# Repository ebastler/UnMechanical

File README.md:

# UnMechanical
 Unmechanical is an attempt to create a capacitive touch keyboard, replacing switches with touchpads.

 The operating principle is pretty much unchanged from the EC boards by [cipulot](https://github.com/Cipulot). Basically, the columns are strobed by the MCU, and the capacitive touchpad forms a capacitive voltage divider together with a 220pF resistor on the PCB. The voltage over the capacitor is measured to determine the capacity of the touchpad, which strongly changes if the pad is touched.

 In order to be able to scan multiple rows, the board uses an analog mux chip that switches from row to row. The input signal is amplified by an OPAMP, since QMK does not offer support for the STM32G431 built-in OPAMPs yet.

## Sweepish
So far, this repository contains a single board, "Sweepish", which consists of a Sweep 3x5 alpha cluster, and a modified 3 key thumb cluster. 

### Features:
* 36 capacitive touch-keys (Layout similar to Sweep)
* Magnetic split connect, allowing for unibody-use
* USB-C PD peripheral of the STM32G431 chip connected to USB-C port
* Circuitry and hole in PCB to mount a Switch Joycon haptic actuator and use it for typing feedback

The board is designed to be used as a unibody, held together by HytePro M411P magnetic pogo connectors, but can also be made into a "proper" split board by using a magnetic cable assembly instead.

Firmware support, as well as some optimizations to make the board nicer to use, are still being worked on (so far it can only work as a single half, split EC keyscan does not work yet). The repo is only published as a proof-of-concept - more or less what the entire board design was for, in the first place. 

This keyboard also uses the USB-C PD peripheral of the STM32G431 since I wanted to make a test-board to experiment using it.

### Pictures

A short video showing the board in action can be found on my youtube channel: https://youtu.be/7uHqJic0PQ8

## Thanks
* [cipulot](https://github.com/Cipulot) for his EC boards, EC QMK keyscan firmwares and help in developing this PCB
* [PCBWay](https://www.pcbway.com/) for the gorgeous sponsored PCBs - couldn't have done it without you!

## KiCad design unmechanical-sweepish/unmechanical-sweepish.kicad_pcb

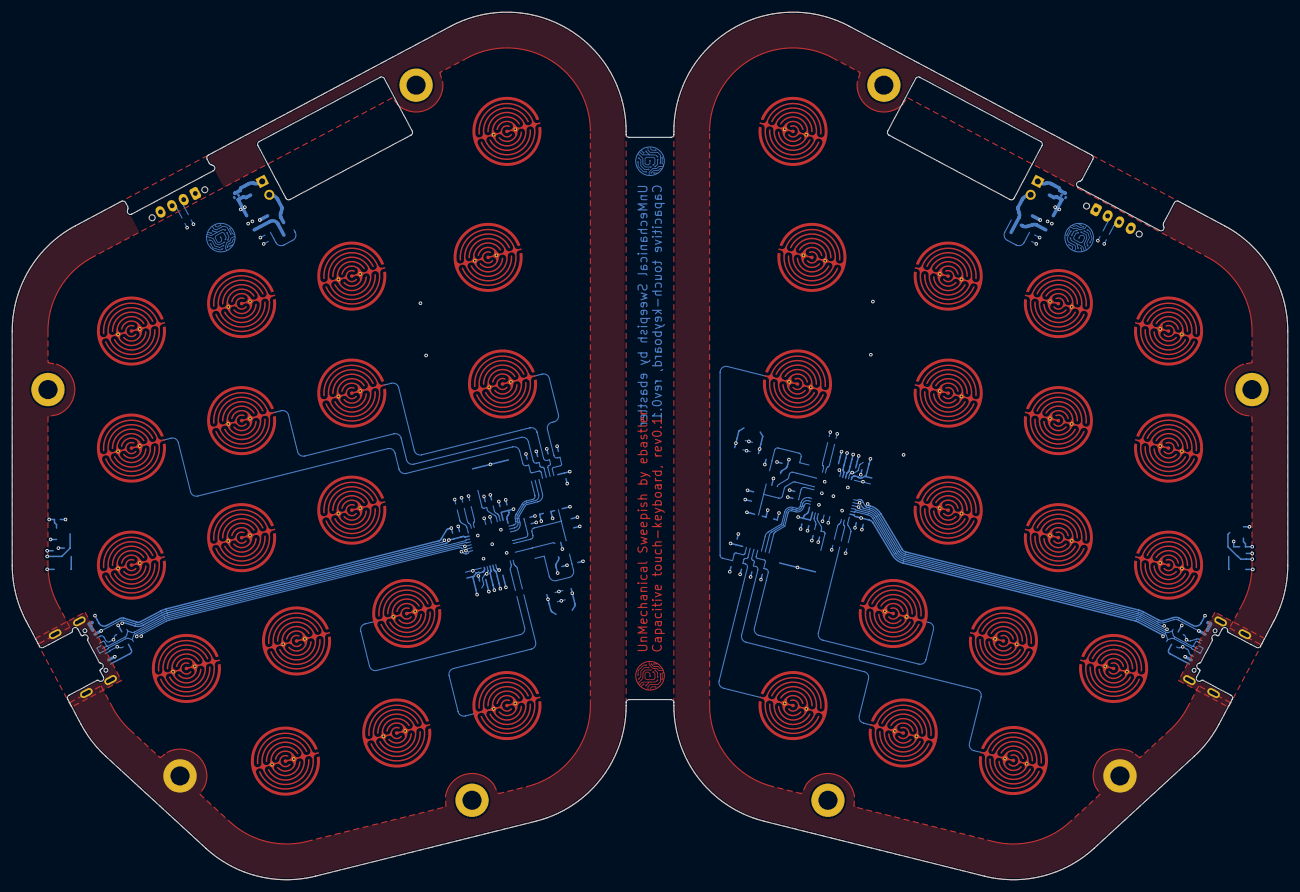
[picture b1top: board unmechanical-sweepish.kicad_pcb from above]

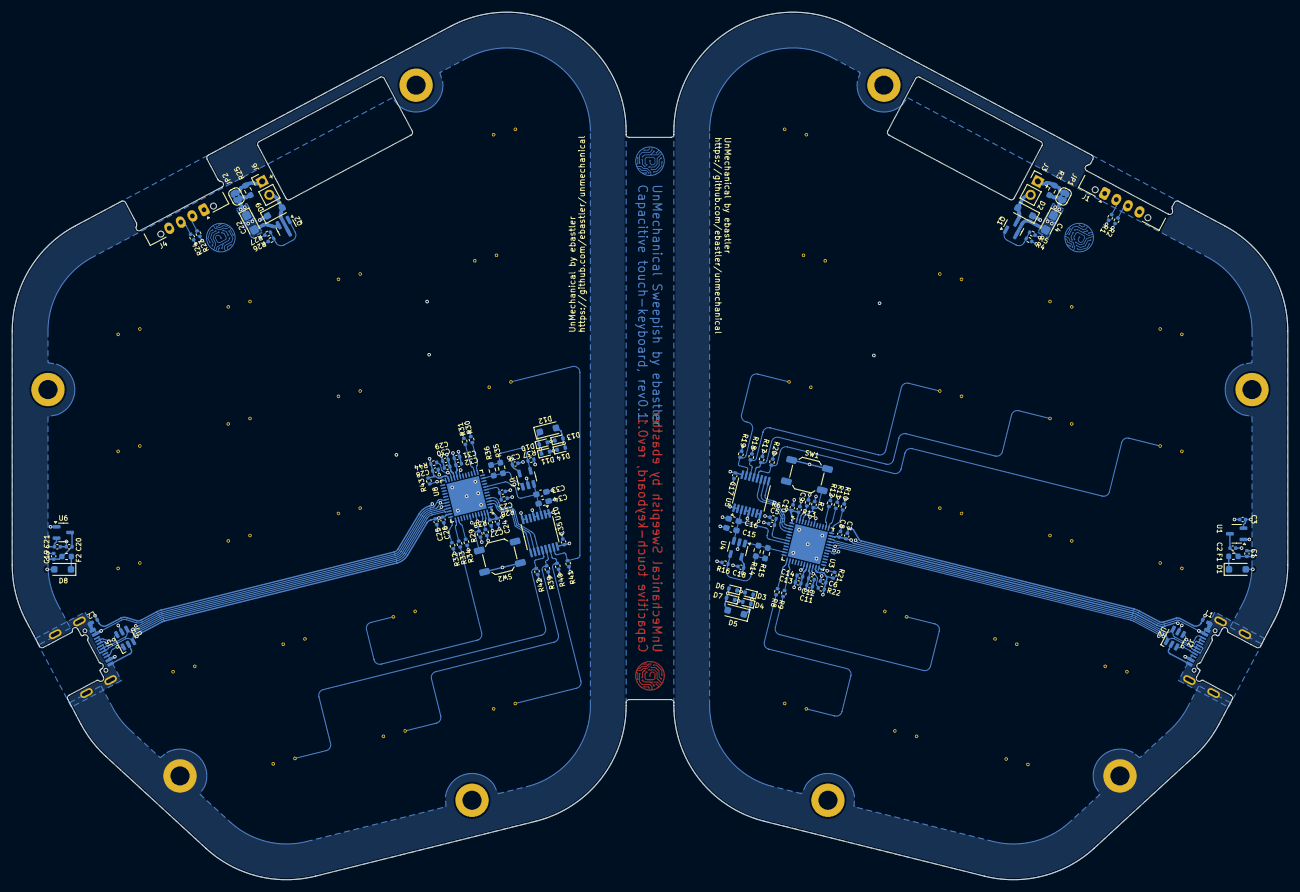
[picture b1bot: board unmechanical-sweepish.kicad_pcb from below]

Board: 4 copper layers, 214.0 x 145.5 mm, 164 parts (120 on the bottom side), 82 nets.

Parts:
C1, C7, C19, C25: 4u7; C_0402_1005Metric
C2, C3, C11, C13, C20, C21, C29, C31: 1u; C_0402_1005Metric
C4, C22: 10u; CP_EIA-3216-10_Kemet-I
C5, C6, C8, C9, C10, C14, C17, C18, C23, C24, C26, C27, C28, C32, C35, C36: 100n; C_0402_1005Metric
C12, C30: 10n; C_0402_1005Metric
C15, C33: DNP; C_0603_1608Metric_Pad1.08x0.95mm_HandSolder
C16, C34: 220p; C_0603_1608Metric_Pad1.08x0.95mm_HandSolder
D1, D2, D8, D9: D_Schottky; D_SOD-123F
D3, D4, D6, D7, D10, D11, D13, D14: 1N4148WT; D_SOD-523
D5, D12: SMF3.3; D_SOD-123F
EC1, EC2, EC3, EC4, EC5, EC6, EC7, EC8, EC9, EC10, EC11, EC12, EC13, EC14, EC15, EC16, EC17, EC18, EC19, EC20, EC21, EC22, EC23, EC24, EC25, EC26, EC27, EC28, EC29, EC30, EC31, EC32, EC33, EC34, EC35, EC36: EC; capsense_finger_1
F1, F2: Polyfuse; Fuse_0603_1608Metric
H1, H2, H3, H4, H5, H6, H7, H8: screw; MountingHole_3.2mm_M3_DIN965_Pad
J1: HytePro M; CON_HytePro_M411P_Plug_1x04-P2.20mm_Horizontal_FlushMount
J2, J5: USB_C_Receptacle_USB2.0; USB_C_Receptacle_HRO_TYPE-C-31-M-14
J3, J6: M; PinHeader_1x02_P2.54mm_Vertical
J4: HytePro F; CON_HytePro_M411P_Receptacle_1x04-P2.20mm_Horizontal_FlushM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
JP1, JP2: JP; SolderJumper-2_P1.3mm_Bridged2Bar_RoundedPad1.0x1.5mm
L1, L2: BLM15PX121SN1D; L_0402_1005Metric
Q1, Q2: AO3400A; SOT-23
R1, R2, R4, R8, R9, R10, R11, R12, R23, R24, R26, R30, R31, R32, R33, R34: 100R; R_0402_1005Metric
R3, R25: 4R7; R_0603_1608Metric_Pad0.98x0.95mm_HandSolder
R5, R6, R7, R13, R27, R28, R29, R38: 10k; R_0402_1005Metric
R14, R35: 100k; R_0603_1608Metric_Pad0.98x0.95mm_HandSolder
R15, R36: DNP; R_0603_1608Metric_Pad0.98x0.95mm_HandSolder
R16, R37: 1k; R_0402_1005Metric
R17, R18, R19, R20, R39, R40, R41, R42: 100k; R_0402_1005Metric
R21, R22, R43, R44: 4k7; R_0402_1005Metric
SW1, SW2: B/R; SW_SPST_SKQG_WithStem
U1, U6: XC6206PxxxMR; SOT-23-3
U2, U7: SRV05-4; SOT-23-6-routable
U3, U8: STM32G431CBUx; QFN-48-1EP_7x7mm_P0.5mm_EP5.6x5.6mm
U4, U9: OPA340NA; SOT-23-5
U5, U10: 74HC4051; TSSOP-16_4.4x5mm_P0.65mm

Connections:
+3.3V: C21.1, C24.1, C25.1, C26.1, C27.1, C28.1, C29.1, C30.1, C31.1, C32.1, C35.1, C36.1, D10.1 (K), D11.1 (K), D12.1 (K), R28.1, R43.1, R44.1, SW2.1, U6.2 (VO), U8.1 (VBAT), U8.20 (VREF+), U8.21 (VDDA), U8.23 (VDD), U8.35 (VDD), U8.48 (VDD), U9.5 (V+), U10.16 (VCC)
+3V3: C3.1, C6.1, C7.1, C8.1, C9.1, C10.1, C11.1, C12.1, C13.1, C14.1, C17.1, C18.1, D3.1 (K), D4.1 (K), D5.1 (K), R6.1, R13.2, R21.1, R22.1, SW1.1, U1.2 (VO), U3.1 (VBAT), U3.20 (VREF+), U3.21 (VDDA), U3.23 (VDD), U3.35 (VDD), U3.48 (VDD), U4.5 (V+), U5.16 (VCC)
+5V: C1.1, C2.1, C4.1, D2.1 (K), F1.2, J1.1, JP1.2 (B), R3.1, U1.3 (VI), U2.5 (VP)
+5VL: C19.1, C20.1, C22.1, D9.1 (K), F2.2, J4.1, JP2.2 (B), R25.1, U6.3 (VI), U7.5 (VP)
/unmechanical-sweepish-l/ADC: R14.2, R15.2, U3.11 (PA3), U4.1
/unmechanical-sweepish-l/BOOT0: R7.1, SW1.2, U3.46 (PB8)
/unmechanical-sweepish-l/CC1: J2.A5 (CC1), U2.3 (IO2), U3.31 (PA9), U3.44 (PB6)
/unmechanical-sweepish-l/CC2: J2.B5 (CC2), U2.4 (IO3), U3.32 (PA10), U3.42 (PB4)
/unmechanical-sweepish-l/USART3_RX: D3.2 (A), D6.1 (K), R2.1, R21.2, U3.24 (PB11)
/unmechanical-sweepish-l/USART3_TX: D4.2 (A), D7.1 (K), R1.1, R22.2, U3.22 (PB10)
/unmechanical-sweepish-l/USBGND: H1.1, J2.A1 (GND), J2.A12 (GND), J2.B1 (GND), J2.B12 (GND), J2.S1 (SHIELD), L1.1, U2.2 (VN)
/unmechanical-sweepish-l/USB_D+: J2.A6 (D+), J2.B6 (D+), U2.6 (IO4), U3.34 (PA12)
/unmechanical-sweepish-l/USB_D-: J2.A7 (D-), J2.B7 (D-), U2.1 (IO1), U3.33 (PA11)
/unmechanical-sweepish-l/VBUS: D1.2 (A), J2.A4 (VBUS), J2.A9 (VBUS), J2.B4 (VBUS), J2.B9 (VBUS), U3.30 (PA8)
/unmechanical-sweepish-l/amux_sel_0: U3.4 (PC15), U5.11 (S0)
/unmechanical-sweepish-l/amux_sel_1: U3.3 (PC14), U5.10 (S1)
/unmechanical-sweepish-l/amux_sel_2: U3.2 (PC13), U5.9 (S2)
/unmechanical-sweepish-l/aplex_out: C15.1, C16.1, U3.8 (PA0), U4.3 (+), U5.3 (A)
/unmechanical-sweepish-l/c0: EC1.2 (B), EC6.2 (B), EC11.2 (B), R8.2
/unmechanical-sweepish-l/c1: EC2.2 (B), EC7.2 (B), EC12.2 (B), R9.2
/unmechanical-sweepish-l/c2: EC3.2 (B), EC8.2 (B), EC13.2 (B), EC16.2 (B), R12.2
/unmechanical-sweepish-l/c3: EC4.2 (B), EC9.2 (B), EC14.2 (B), EC17.2 (B), R11.2
/unmechanical-sweepish-l/c4: EC5.2 (B), EC10.2 (B), EC15.2 (B), EC18.2 (B), R10.2
/unmechanical-sweepish-l/handsense: R13.1, U3.47 (PB9)
/unmechanical-sweepish-l/hapt: R4.1, U3.19 (PB2)
/unmechanical-sweepish-l/nRST: C5.2, R6.2, U3.7 (PG10)
/unmechanical-sweepish-l/r0: EC1.1 (A), EC2.1 (A), EC3.1 (A), EC4.1 (A), EC5.1 (A), R20.1, U5.12 (A3)
/unmechanical-sweepish-l/r1: EC6.1 (A), EC7.1 (A), EC8.1 (A), EC9.1 (A), EC10.1 (A), R17.1, U5.13 (A0)
/unmechanical-sweepish-l/r2: EC11.1 (A), EC12.1 (A), EC13.1 (A), EC14.1 (A), EC15.1 (A), R18.1, U5.14 (A1)
/unmechanical-sweepish-l/r3: EC16.1 (A), EC17.1 (A), EC18.1 (A), R19.1, U5.15 (A2)
/unmechanical-sweepish-r/ADC: R35.2, R36.2, U8.11 (PA3), U9.1
/unmechanical-sweepish-r/BOOT0: R29.1, SW2.2, U8.46 (PB8)
/unmechanical-sweepish-r/CC1: J5.A5 (CC1), U7.6 (IO4), U8.31 (PA9), U8.44 (PB6)
/unmechanical-sweepish-r/CC2: J5.B5 (CC2), U7.1 (IO1), U8.32 (PA10), U8.42 (PB4)
/unmechanical-sweepish-r/USART3_RX: D10.2 (A), D13.1 (K), R24.1, R43.2, U8.24 (PB11)
/unmechanical-sweepish-r/USART3_TX: D11.2 (A), D14.1 (K), R23.1, R44.2, U8.22 (PB10)
/unmechanical-sweepish-r/USBGND: H5.1, J5.A1 (GND), J5.A12 (GND), J5.B1 (GND), J5.B12 (GND), J5.S1 (SHIELD), L2.1, U7.2 (VN)
/unmechanical-sweepish-r/USB_D+: J5.A6 (D+), J5.B6 (D+), U7.3 (IO2), U8.34 (PA12)
/unmechanical-sweepish-r/USB_D-: J5.A7 (D-), J5.B7 (D-), U7.4 (IO3), U8.33 (PA11)
/unmechanical-sweepish-r/VBUS: D8.2 (A), J5.A4 (VBUS), J5.A9 (VBUS), J5.B4 (VBUS), J5.B9 (VBUS), U8.30 (PA8)
/unmechanical-sweepish-r/amux_sel_0: U8.4 (PC15), U10.11 (S0)
/unmechanical-sweepish-r/amux_sel_1: U8.3 (PC14), U10.10 (S1)
/unmechanical-sweepish-r/amux_sel_2: U8.2 (PC13), U10.9 (S2)
/unmechanical-sweepish-r/aplex_out: C33.1, C34.1, U8.8 (PA0), U9.3 (+), U10.3 (A)
/unmechanical-sweepish-r/c0: EC19.2 (B), EC24.2 (B), EC29.2 (B), EC34.2 (B), R30.2
/unmechanical-sweepish-r/c1: EC20.2 (B), EC25.2 (B), EC30.2 (B), EC35.2 (B), R31.2
/unmechanical-sweepish-r/c2: EC21.2 (B), EC26.2 (B), EC31.2 (B), EC36.2 (B), R34.2
/unmechanical-sweepish-r/c3: EC22.2 (B), EC27.2 (B), EC32.2 (B), R33.2
/unmechanical-sweepish-r/c4: EC23.2 (B), EC28.2 (B), EC33.2 (B), R32.2
/unmechanical-sweepish-r/handsense: R38.1, U8.47 (PB9)
/unmechanical-sweepish-r/hapt: R26.1, U8.19 (PB2)
/unmechanical-sweepish-r/nRST: C23.2, R28.2, U8.7 (PG10)
/unmechanical-sweepish-r/r0: EC19.1 (A), EC20.1 (A), EC21.1 (A), EC22.1 (A), EC23.1 (A), R42.1, U10.12 (A3)
/unmechanical-sweepish-r/r1: EC24.1 (A), EC25.1 (A), EC26.1 (A), EC27.1 (A), EC28.1 (A), R39.1, U10.13 (A0)
/unmechanical-sweepish-r/r2: EC29.1 (A), EC30.1 (A), EC31.1 (A), EC32.1 (A), EC33.1 (A), R40.1, U10.14 (A1)
/unmechanical-sweepish-r/r3: EC34.1 (A), EC35.1 (A), EC36.1 (A), R41.1, U10.15 (A2)
GND: C1.2, C2.2, C3.2, C4.2, C5.1, C6.2, C7.2, C8.2, C9.2, C10.2, C11.2, C12.2, C13.2, C14.2, C15.2, C16.2, C17.2, C18.2, D5.2 (A), D6.2 (A), D7.2 (A), J1.4, L1.2, Q1.2 (S), R5.2, R7.2, R16.2, R17.2, R18.2, R19.2, R20.2, U1.1 (GND), U3.49 (VSS), U4.2 (V-), U5.1 (A4), U5.2 (A6), U5.4 (A7), U5.5 (A5), U5.7 (VEE), U5.8 (GND)
GND1: C19.2, C20.2, C21.2, C22.2, C23.1, C24.2, C25.2, C26.2, C27.2, C28.2, C29.2, C30.2, C31.2, C32.2, C33.2, C34.2, C35.2, C36.2, D12.2 (A), D13.2 (A), D14.2 (A), J4.4, L2.2, Q2.2 (S), R27.2, R29.2, R37.2, R38.2, R39.2, R40.2, R41.2, R42.2, U6.1 (GND), U8.49 (VSS), U9.2 (V-), U10.1 (A4), U10.2 (A6), U10.4 (A7), U10.5 (A5), U10.7 (VEE), U10.8 (GND)
unnamed: D1.1 (K), F1.1
unnamed: D2.2 (A), J3.2, Q1.3 (D)
unnamed: D8.1 (K), F2.1
unnamed: D9.2 (A), J6.2, Q2.3 (D)
unnamed: J1.2, R1.2
unnamed: J1.3, R2.2
unnamed: J3.1, JP1.1 (A), R3.2
unnamed: J4.2, R23.2
unnamed: J4.3, R24.2
unnamed: J6.1, JP2.1 (A), R25.2
unnamed: Q1.1 (G), R4.2, R5.1
unnamed: Q2.1 (G), R26.2, R27.1
unnamed: R8.1, U3.13 (PA5)
unnamed: R9.1, U3.14 (PA6)
unnamed: R10.1, U3.36 (PA13)
unnamed: R11.1, U3.37 (PA14)
unnamed: R12.1, U3.38 (PA15)
unnamed: R14.1, R15.1, R16.1, U4.4 (-)
unnamed: R30.1, U8.13 (PA5)
unnamed: R31.1, U8.14 (PA6)
unnamed: R32.1, U8.36 (PA13)
unnamed: R33.1, U8.37 (PA14)
unnamed: R34.1, U8.38 (PA15)
unnamed: R35.1, R36.1, R37.1, U9.4 (-)

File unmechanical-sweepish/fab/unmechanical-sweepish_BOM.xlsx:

Item | Reference(s) | Qty | Manufacturer | Manufacturer Part # | Value | Description | Footprint | Type | Notes
1 | C1, C7, C19, C25 | 4 |  |  | 4u7 | 4.7 uF ceramic capacitor, X5R or X7R, 10V, ± 20% or lower | C_0402 | SMD | Manufacturer does not matter
2 | C2, C3, C11, C13, C20, C21, C29, C31 | 8 |  |  | 1u | 1 uF ceramic capacitor, X5R or X7R, 10V, ± 20% or lower | C_0402 | SMD | Manufacturer does not matter
3 | C4, C22 | 2 |  |  | 10u | 10 uF tantalum capacitor, 16V or higher, ± 20% or lower | CP_3216-10_Kemet-A | SMD | Manufacturer does not matter
4 | C5, C6, C8, C9, C10, C14, C17, C18, C23, C24, C26, C27, C28, C32, C35, C36 | 16 |  |  | 100n | 100 nF ceramic capacitor, X5R or X7R, 10V or higher, ± 20% or lower | C_0402 | SMD | Manufacturer does not matter
5 | C12, C30 | 2 |  |  | 10n | 10 nF ceramic capacitor, X5R or X7R, 10V or higher, ± 20% or lower | C_0402 | SMD | Manufacturer does not matter
6 | C15, C33 | 2 |  | DNP | DNP |  | C_0603 | SMD | Do not populate
7 | C16, C34 | 2 |  |  | 220p | 220 pF ceramic capacitor, C0G, 10V or higher, ± 5% | C_0603 | SMD | Manufacturer does not matter
8 | D1, D2, D8, D9 | 4 |  | DS14W |  | 40 V 1 A Schottky diode | D_SOD-123F | SMD | Manufacturer does not matter
9 | D3, D4, D6, D7, D10, D11, D13, D14 | 8 |  | 1N4148WT |  |  | D_SOD-523 | SMD | Manufacturer does not matter
10 | D5, D12 | 2 |  | SMF3.3 |  | 3.3 V TVS diode | D_SOD-123F | SMD | Manufacturer does not matter
11 | F1, F2 | 2 | BHFUSE | BSMD0603-050-6V | 500 mA | 500 mA 6 V resettable polyfuse | Fuse_0603 | SMD | Manufacturer does not matter, other parts of similar specs can be used as repla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
12 | J1 | 1 | HytePro | HTP-CON-M411P-F |  | Spring-loaded magnetic connector | CON_HytePro_M411P_Plug | THT | J1 and J4 are sold as a pair: https://www.hyte.pro/product/m411p.html. Please m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
13 | J2, J5 | 2 | HRO Koreaparts | TYPE-C-31-M-14 |  | USB-C receptacle | USB_C_Receptacle_HRO_TYPE-C-31-M-14 | SMD/THT
14 | J4 | 1 | HytePro | HTP-CON-M411P-M |  | Spring-loaded magnetic connector | CON_HytePro_M411P_Receptacle | THT | J1 and J4 are sold as a pair: https://www.hyte.pro/product/m411p.html. Please m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
15 | L1, L2 | 2 | MuRata | BLM15PX121SN1D |  | Ferrite bead 2A 55 mOhm 120Ohm @ 100MHz | L_0402 | SMD
16 | Q1, Q2 | 2 | Alpha & Omega Semiconductor | AO3400A |  | 30 V 5.7 A n-ch MOSFET | SOT-23-3 | SMD
17 | R1, R2, R4, R8, R9, R10, R11, R12, R23, R24, R26, R30, R31, R32, R33, R34 | 16 |  |  | 100R | 100 Ohm 1/16W SMD resistor, ± 1% | R_0402 | SMD | Manufacturer does not matter
18 | R3, R25 | 2 |  |  | 4R7 | 4.7 Ohm 1/16W SMD resistor, ± 1% | R_0603 | SMD | Manufacturer does not matter
19 | R5, R6, R7, R13, R27, R28, R29, R38 | 8 |  |  | 10k | 10 kOhm 1/16W SMD resistor, ± 1% | R_0402 | SMD | Manufacturer does not matter
20 | R14, R35 | 2 |  |  | 100k | 100 kOhm 1/16W SMD resistor, ± 1% | R_0603 | SMD | Manufacturer does not matter
21 | R15, R36 | 2 |  | DNP | DNP |  | R_0603 | SMD | Do not populate
22 | R16, R37 | 2 |  |  | 1k | 1 kOhm 1/16W SMD resistor, ± 1% | R_0402 | SMD | Manufacturer does not matter
23 | R17, R18, R19, R20, R39, R40, R41, R42 | 8 |  |  | 100k | 100 kOhm 1/16W SMD resistor, ± 1% | R_0402 | SMD | Manufacturer does not matter
24 | R21, R22, R43, R44 | 4 |  |  | 4k7 | 4.7 kOhm 1/16W SMD resistor, ± 1% | R_0402 | SMD | Manufacturer does not matter
25 | SW1, SW2 | 2 | Alps Alpine | SKQGAKE010 |  | Alps SMD push button | SW_SPST_SKQG | SMD | All SKQGA*E010 models are acceptable as substitutes
26 | U1, U6 | 2 | Torex Semiconductor | XC6206P332MR |  | 3.3V low-dropout voltage regulator IC | SOT-23-3 | SMD
27 | U2, U7 | 2 |  | SRV05-4 |  | 4 channel ESD protection device | SOT-23-6 | SMD | Manufacturer does not matter
28 | U3, U8 | 2 | STMicroelectronics | STM32G431CBU6 |  | 32bit ARM Microcontroller | QFN-48-1EP_7x7mm_P0.5mm_EP5.6x5.6mm | SMD
29 | U4, U9 | 2 | Texas Instruments | OPA340NA |  | 1 channel rail-to-rail OPAMP | SOT-23-5 | SMD
30 | U5, U10 | 2 | Nexperia | 74HC4051PW,118 |  | 8bit analog Analog Switch/Multiplexer | TSSOP-16_4.4x5mm_P0.65mm | SMD

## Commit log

2024-08-02 Fix gitignore
2024-08-03 update to kicad 8 model paths
2024-08-03 remove outdated graphics on user.drawings as reported in #2
